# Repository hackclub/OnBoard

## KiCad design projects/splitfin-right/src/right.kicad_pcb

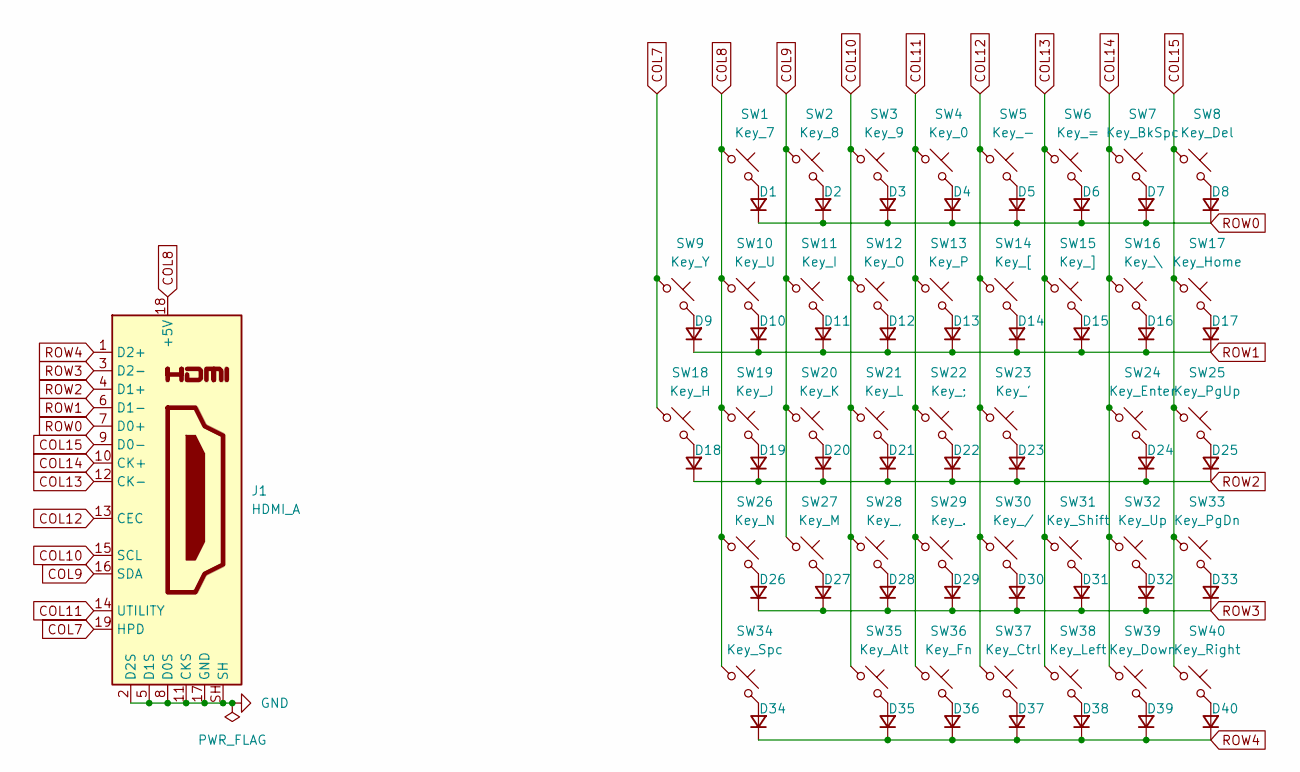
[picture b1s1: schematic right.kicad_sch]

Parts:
D1, D2, D3, D4, D5, D6, D7, D8, D9, D10, D11, D12, D13, D14, D15, D16, D17, D18, D19, D20, D21, D22, D23, D24, D25, D26, D27, D28, D29, D30, D31, D32, D33, D34, D35, D36, D37, D38, D39, D40: D_SOD-123
J1: HDMI_A; HDMI_A_Amphenol_10029449-x01xLF_Horizontal
SW1: Key_7; SW_Gateron_LowProfile_HotSwap_Good
SW2: Key_8; SW_Gateron_LowProfile_HotSwap_Good
SW3: Key_9; SW_Gateron_LowProfile_HotSwap_Good
SW4: Key_0; SW_Gateron_LowProfile_HotSwap_Good
SW5: Key_-; SW_Gateron_LowProfile_HotSwap_Good
SW6: Key_=; SW_Gateron_LowProfile_HotSwap_Good
SW7: Key_BkSpc; SW_Gateron_LowProfile_HotSwap_Good
SW8: Key_Del; SW_Gateron_LowProfile_HotSwap_Good
SW9: Key_Y; SW_Gateron_LowProfile_HotSwap_Good
SW10: Key_U; SW_Gateron_LowProfile_HotSwap_Good
SW11: Key_I; SW_Gateron_LowProfile_HotSwap_Good
SW12: Key_O; SW_Gateron_LowProfile_HotSwap_Good
SW13: Key_P; SW_Gateron_LowProfile_HotSwap_Good
SW14: Key_[; SW_Gateron_LowProfile_HotSwap_Good
SW15: Key_]; SW_Gateron_LowProfile_HotSwap_Good
SW16: Key_\; SW_Gateron_LowProfile_HotSwap_Good
SW17: Key_Home; SW_Gateron_LowProfile_HotSwap_Good
SW18: Key_H; SW_Gateron_LowProfile_HotSwap_Good
SW19: Key_J; SW_Gateron_LowProfile_HotSwap_Good
SW20: Key_K; SW_Gateron_LowProfile_HotSwap_Good
SW21: Key_L; SW_Gateron_LowProfile_HotSwap_Good
SW22: Key_;; SW_Gateron_LowProfile_HotSwap_Good
SW23: Key_'; SW_Gateron_LowProfile_HotSwap_Good
SW24: Key_Enter; SW_Gateron_LowProfile_HotSwap_Good
SW25: Key_PgUp; SW_Gateron_LowProfile_HotSwap_Good
SW26: Key_N; SW_Gateron_LowProfile_HotSwap_Good
SW27: Key_M; SW_Gateron_LowProfile_HotSwap_Good
SW28: Key_,; SW_Gateron_LowProfile_HotSwap_Good
SW29: Key_.; SW_Gateron_LowProfile_HotSwap_Good
SW30: Key_/; SW_Gateron_LowProfile_HotSwap_Good
SW31: Key_Shift; SW_Gateron_LowProfile_HotSwap_Good
SW32: Key_Up; SW_Gateron_LowProfile_HotSwap_Good
SW33: Key_PgDn; SW_Gateron_LowProfile_HotSwap_Good
SW34: Key_Spc; SW_Gateron_LowProfile_HotSwap_Good
SW35: Key_Alt; SW_Gateron_LowProfile_HotSwap_Good
SW36: Key_Fn; SW_Gateron_LowProfile_HotSwap_Good
SW37: Key_Ctrl; SW_Gateron_LowProfile_HotSwap_Good
SW38: Key_Left; SW_Gateron_LowProfile_HotSwap_Good
SW39: Key_Down; SW_Gateron_LowProfile_HotSwap_Good
SW40: Key_Right; SW_Gateron_LowProfile_HotSwap_Good

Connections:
COL7: J1.19 (HPD), SW9.1, SW18.1
COL8: J1.18 (+5V), SW1.1, SW10.1, SW19.1, SW26.1, SW34.1
COL9: J1.16 (SDA), SW2.1, SW11.1, SW20.1, SW27.1
COL10: J1.15 (SCL), SW3.1, SW12.1, SW21.1, SW28.1, SW35.1
COL11: J1.14 (UTILITY), SW4.1, SW13.1, SW22.1, SW29.1, SW36.1
COL12: J1.13 (CEC), SW5.1, SW14.1, SW23.1, SW30.1, SW37.1
COL13: J1.12 (CK-), SW6.1, SW15.1, SW31.1, SW38.1
COL14: J1.10 (CK+), SW7.1, SW16.1, SW24.1, SW32.1, SW39.1
COL15: J1.9 (D0-), SW8.1, SW17.1, SW25.1, SW33.1, SW40.1
GND: J1.2 (D2S), J1.5 (D1S), J1.8 (D0S), J1.11 (CKS), J1.17 (GND), J1.SH
unnamed: D1.2 (A), SW1.2
unnamed: D2.2 (A), SW2.2
unnamed: D3.2 (A), SW3.2
unnamed: D4.2 (A), SW4.2
unnamed: D5.2 (A), SW5.2
unnamed: D6.2 (A), SW6.2
unnamed: D7.2 (A), SW7.2
unnamed: D8.2 (A), SW8.2
unnamed: D9.2 (A), SW9.2
unnamed: D10.2 (A), SW10.2
unnamed: D11.2 (A), SW11.2
unnamed: D12.2 (A), SW12.2
unnamed: D13.2 (A), SW13.2
unnamed: D14.2 (A), SW14.2
unnamed: D15.2 (A), SW15.2
unnamed: D16.2 (A), SW16.2
unnamed: D17.2 (A), SW17.2
unnamed: D18.2 (A), SW18.2
unnamed: D19.2 (A), SW19.2
unnamed: D20.2 (A), SW20.2
unnamed: D21.2 (A), SW21.2
unnamed: D22.2 (A), SW22.2
unnamed: D23.2 (A), SW23.2
unnamed: D24.2 (A), SW24.2
unnamed: D25.2 (A), SW25.2
unnamed: D26.2 (A), SW26.2
unnamed: D27.2 (A), SW27.2
unnamed: D28.2 (A), SW28.2
unnamed: D29.2 (A), SW29.2
unnamed: D30.2 (A), SW30.2
unnamed: D31.2 (A), SW31.2
unnamed: D32.2 (A), SW32.2
unnamed: D33.2 (A), SW33.2
unnamed: D34.2 (A), SW34.2
unnamed: D35.2 (A), SW35.2
unnamed: D36.2 (A), SW36.2
unnamed: D37.2 (A), SW37.2
unnamed: D38.2 (A), SW38.2
unnamed: D39.2 (A), SW39.2
unnamed: D40.2 (A), SW40.2
ROW0: D1.1 (K), D2.1 (K), D3.1 (K), D4.1 (K), D5.1 (K), D6.1 (K), D7.1 (K), D8.1 (K), J1.7 (D0+)
ROW1: D9.1 (K), D10.1 (K), D11.1 (K), D12.1 (K), D13.1 (K), D14.1 (K), D15.1 (K), D16.1 (K), D17.1 (K), J1.6 (D1-)
ROW2: D18.1 (K), D19.1 (K), D20.1 (K), D21.1 (K), D22.1 (K), D23.1 (K), D24.1 (K), D25.1 (K), J1.4 (D1+)
ROW3: D26.1 (K), D27.1 (K), D28.1 (K), D29.1 (K), D30.1 (K), D31.1 (K), D32.1 (K), D33.1 (K), J1.3 (D2-)
ROW4: D34.1 (K), D35.1 (K), D36.1 (K), D37.1 (K), D38.1 (K), D39.1 (K), D40.1 (K), J1.1 (D2+)

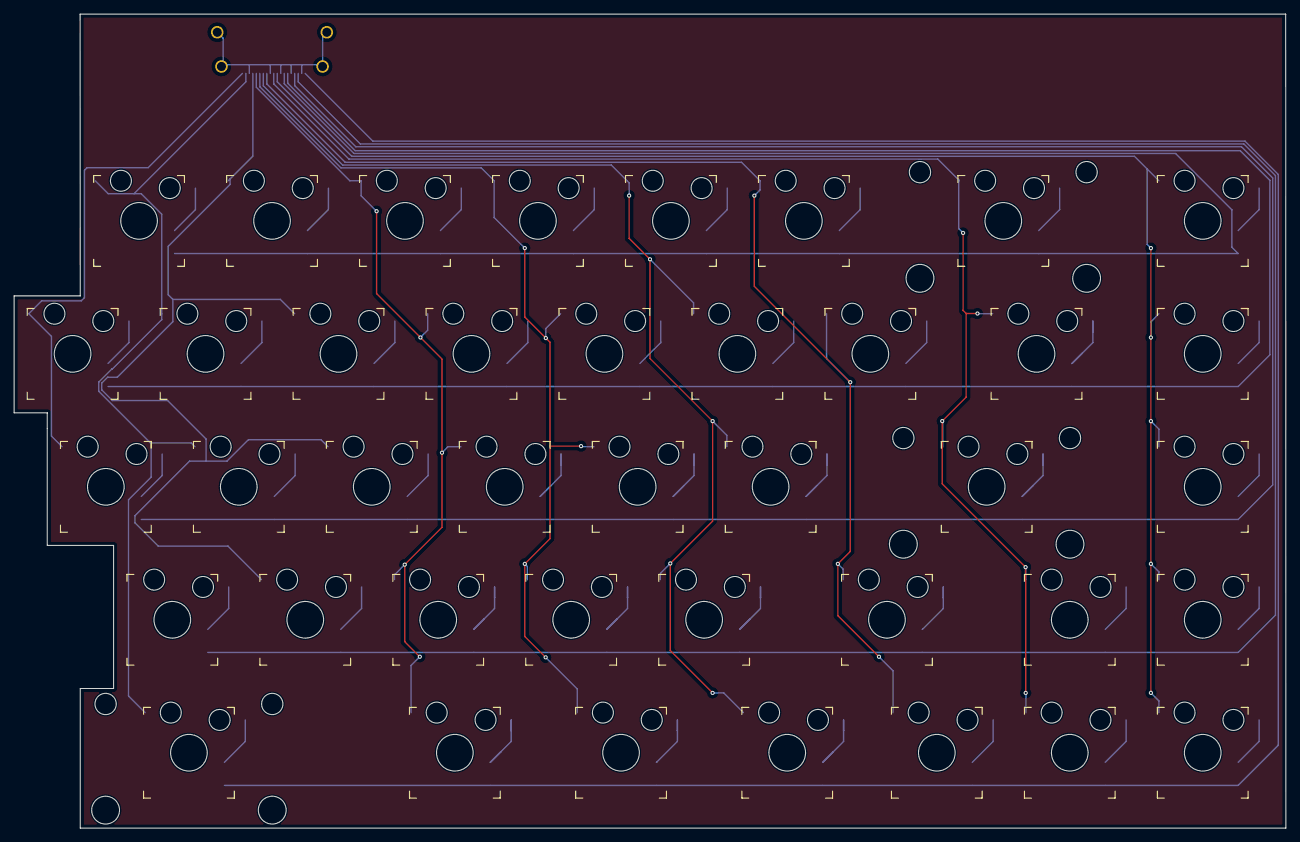
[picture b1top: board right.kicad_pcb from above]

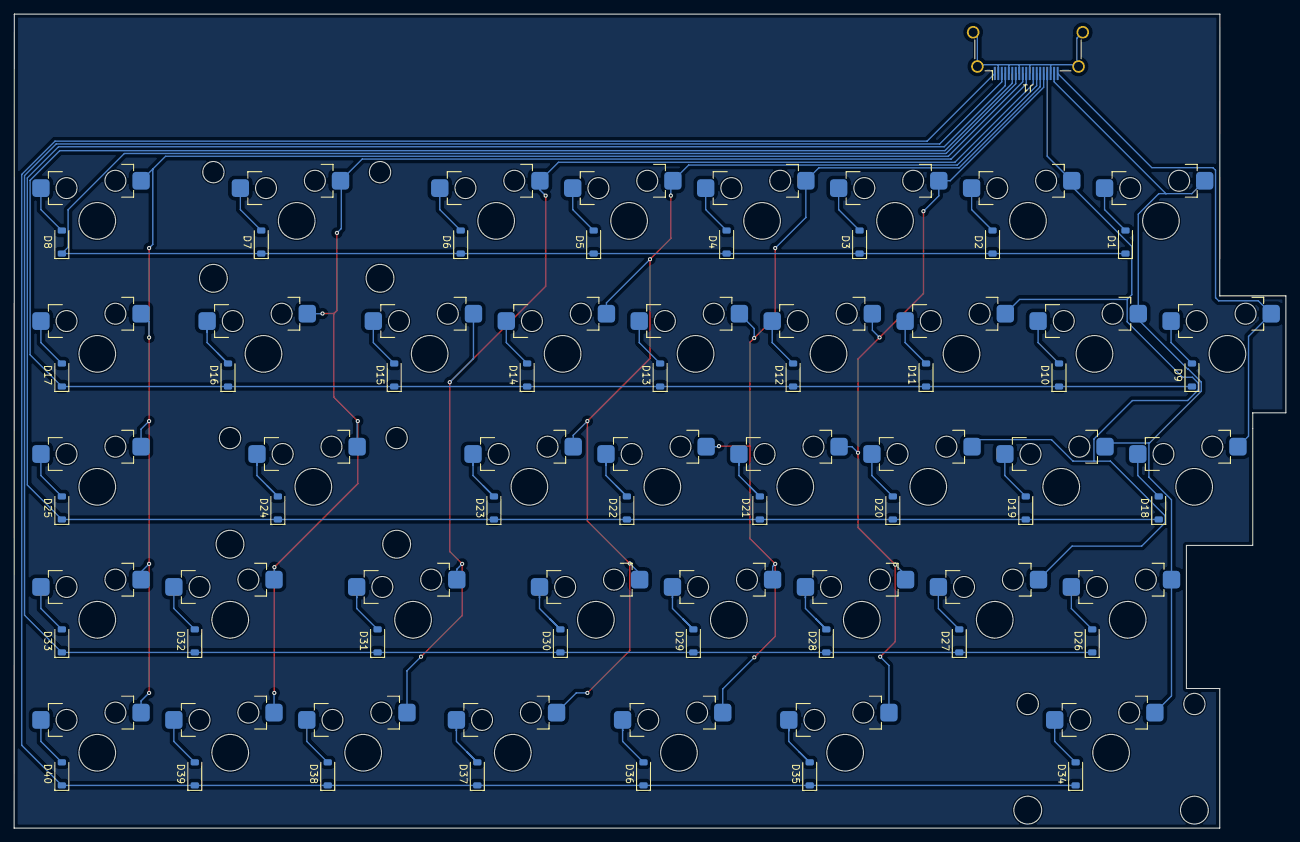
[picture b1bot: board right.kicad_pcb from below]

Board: 2 copper layers, 182.2 x 116.6 mm, 84 parts (41 on the bottom side), 55 nets.

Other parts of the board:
ST7, ST24, ST34: Stabilizer_Cherry_MX_2.00u

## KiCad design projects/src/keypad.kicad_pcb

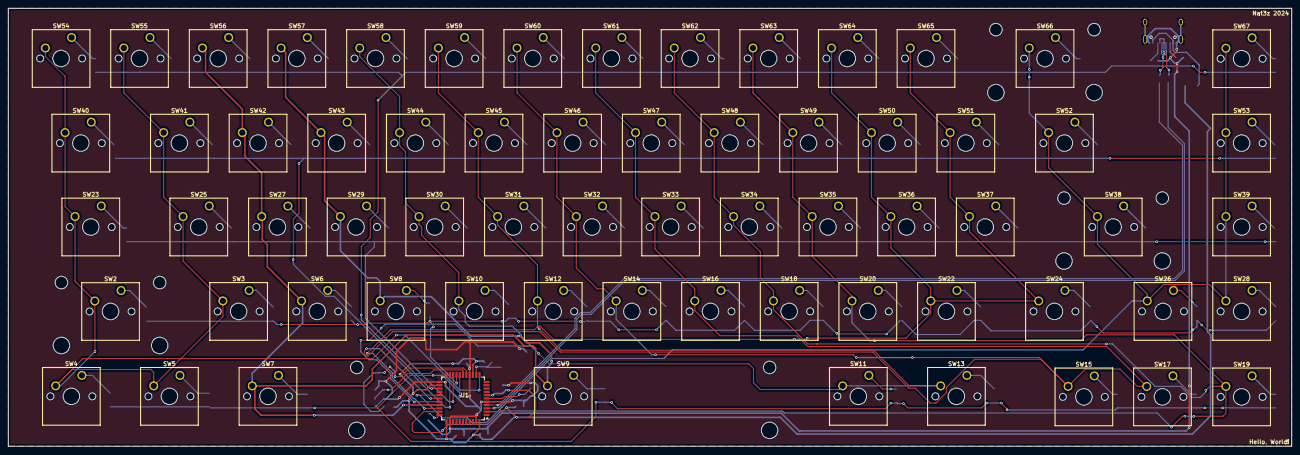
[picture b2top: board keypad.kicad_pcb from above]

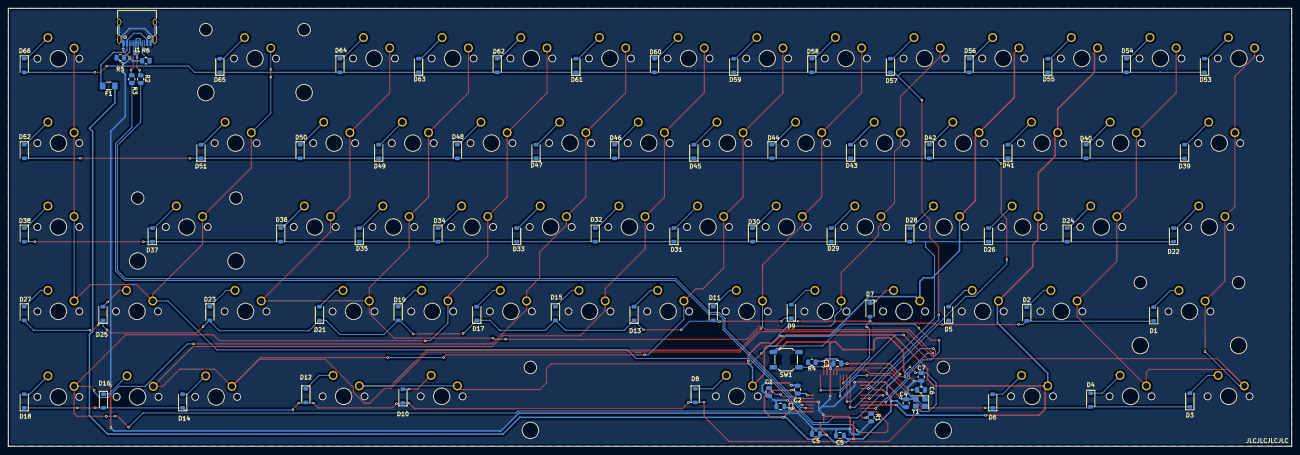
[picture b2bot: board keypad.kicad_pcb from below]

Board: 2 copper layers, 310.8 x 106.1 mm, 150 parts (84 on the bottom side), 90 nets.

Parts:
C1: 1uF; C_0805_2012Metric
C2, C2#2, C3, C4: 0.1uF; C_0805_2012Metric
C5, C5#2: 10uF; C_0805_2012Metric
C6, C7: 22pF; C_0805_2012Metric
D1, D2, D3, D4, D5, D6, D7, D8, D9, D10, D11, D12, D13, D14, D15, D16, D17, D18, D19, D21, D22, D23, D24, D25, D26, D27, D28, D29, D30, D31, D32, D33, D34, D35, D36, D37, D38, D39, D40, D41, D42, D43, D44, D45, D46, D47, D48, D49, D50, D51, D52, D53, D54, D55, D56, D57, D58, D59, D60, D61, D62, D63, D64, D65, D66: D; D_SOD-123
F1: Polyfuse_Small; Fuse_1206_3216Metric_Pad1.42x1.75mm_HandSolder
J1: USB_C_Receptacle; USB_C_Receptacle_HRO_TYPE-C-31-M-12
R1, R4: 10k; R_0805_2012Metric
R2, R3: 22; R_0805_2012Metric
R5, R6: 5.1k; R_0805_2012Metric
SW1: SW_Push; SW_SPST_SKQG_WithStem
SW2, SW38: SW_Push; SW_Cherry_MX_2.25u_PCB
SW3, SW6, SW8, SW10, SW12, SW14, SW15, SW16, SW17, SW18, SW19, SW20, SW22, SW25, SW26, SW27, SW28, SW29, SW30, SW31, SW32, SW33, SW34, SW35, SW36, SW37, SW39, SW41, SW42, SW43, SW44, SW45, SW46, SW47, SW48, SW49, SW50, SW51, SW53, SW54, SW55, SW56, SW57, SW58, SW59, SW60, SW61, SW62, SW63, SW64, SW65, SW67: SW_Push; SW_Cherry_MX_1.00u_PCB
SW4, SW5, SW7, SW11, SW13: SW_Push; SW_Cherry_MX_1.25u_PCB
SW9: SW_Push; SW_Cherry_MX_6.25u_PCB
SW23, SW24: SW_Push; SW_Cherry_MX_1.75u_PCB
SW40, SW52: SW_Push; SW_Cherry_MX_1.50u_PCB
SW66: SW_Push; SW_Cherry_MX_2.00u_PCB
U1: ATmega32U4-A; TQFP-44_10x10mm_P0.8mm
Y1: 16MHz; Crystal_SMD_3225-4Pin_3.2x2.5mm

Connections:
+5V: C2.1, C2#2.1, C3.1, C4.1, C5.1, C5#2.1, F1.1, R4.1, U1.2 (UVCC), U1.7 (VBUS), U1.14 (VCC), U1.24 (AVCC), U1.34 (VCC), U1.44 (AVCC)
COL0: SW2.2, SW3.2, SW4.2, SW5.2, SW23.2, SW25.2, SW40.2, SW41.2, SW54.2, SW55.2, U1.12 (PB7)
COL1: D22.1 (K), D24.2 (A), D26.1 (K), D28.2 (A), D29.1 (K), D30.2 (A), D31.1 (K), D32.2 (A), D33.1 (K), D34.2 (A), D35.1 (K), D36.2 (A), D37.1 (K), D38.2 (A), SW6.2, SW7.2, SW8.2, SW9.2, SW27.2, SW29.2, SW42.2, SW43.2, SW56.2, SW57.2, U1.20 (PD2), U1.30 (PB6)
COL2: SW10.2, SW11.2, SW12.2, SW13.2, SW30.2, SW31.2, SW44.2, SW45.2, SW58.2, SW59.2, U1.29 (PB5)
COL3: SW14.2, SW15.2, SW16.2, SW17.2, SW32.2, SW33.2, SW46.2, SW47.2, SW60.2, SW61.2, U1.28 (PB4)
COL4: SW18.2, SW19.2, SW20.2, SW34.2, SW35.2, SW48.2, SW49.2, SW62.2, SW63.2, U1.32 (PC7)
COL5: SW22.2, SW24.2, SW36.2, SW37.2, SW50.2, SW51.2, SW64.2, SW65.2, U1.31 (PC6)
COL6: SW26.2, SW28.2, SW38.2, SW39.2, SW52.2, SW53.2, SW66.2, SW67.2, U1.27 (PD7)
D+: J1.A6 (D+), J1.B6 (D+), R2.1
D-: J1.A7 (D-), J1.B7 (D-), R3.1
GND: C1.2, C2.2, C2#2.2, C3.2, C4.2, C5.2, C5#2.2, C6.1, C7.1, J1.A1 (GND), J1.A12 (GND), J1.B1 (GND), J1.B12 (GND), J1.S1 (SHIELD), R1.2, R5.2, R6.2, SW1.1, U1.5 (UGND), U1.15 (GND), U1.23 (GND), U1.35 (GND), U1.43 (GND), Y1.2, Y1.4
unnamed: D1.2 (A), SW2.1
unnamed: D2.1 (K), SW3.1
unnamed: D3.2 (A), SW4.1
unnamed: D4.1 (K), SW5.1
unnamed: D5.2 (A), SW6.1
unnamed: D6.2 (A), SW7.1
unnamed: D7.1 (K), SW8.1
unnamed: D8.1 (K), SW9.1
unnamed: D9.2 (A), SW10.1
unnamed: D10.2 (A), SW11.1
unnamed: D11.1 (K), SW12.1
unnamed: D12.1 (K), SW13.1
unnamed: D13.2 (A), SW14.1
unnamed: D14.2 (A), SW15.1
unnamed: D15.1 (K), SW16.1
unnamed: D16.1 (K), SW17.1
unnamed: D17.2 (A), SW18.1
unnamed: D18.2 (A), SW19.1
unnamed: D19.1 (K), SW20.1
unnamed: D21.2 (A), SW22.1
unnamed: D22.2 (A), SW23.1
unnamed: D23.1 (K), SW24.1
unnamed: D24.1 (K), SW25.1
unnamed: D25.2 (A), SW26.1
unnamed: D26.2 (A), SW27.1
unnamed: D27.1 (K), SW28.1
unnamed: D28.1 (K), SW29.1
unnamed: D29.2 (A), SW30.1
unnamed: D30.1 (K), SW31.1
unnamed: D31.2 (A), SW32.1
unnamed: D32.1 (K), SW33.1
unnamed: D33.2 (A), SW34.1
unnamed: D34.1 (K), SW35.1
unnamed: D35.2 (A), SW36.1
unnamed: D36.1 (K), SW37.1
unnamed: D37.2 (A), SW38.1
unnamed: D38.1 (K), SW39.1
unnamed: D39.2 (A), SW40.1
unnamed: D40.1 (K), SW41.1
unnamed: D41.2 (A), SW42.1
unnamed: D42.1 (K), SW43.1
unnamed: D43.2 (A), SW44.1
unnamed: D44.1 (K), SW45.1
unnamed: D45.2 (A), SW46.1
unnamed: D46.1 (K), SW47.1
unnamed: D47.2 (A), SW48.1
unnamed: D48.1 (K), SW49.1
unnamed: D49.2 (A), SW50.1
unnamed: D50.1 (K), SW51.1
unnamed: D51.2 (A), SW52.1
unnamed: D52.1 (K), SW53.1
unnamed: D53.2 (A), SW54.1
unnamed: D54.1 (K), SW55.1
unnamed: D55.2 (A), SW56.1
unnamed: D56.1 (K), SW57.1
unnamed: D57.2 (A), SW58.1
unnamed: D58.1 (K), SW59.1
unnamed: D59.2 (A), SW60.1
unnamed: D60.1 (K), SW61.1
unnamed: D61.2 (A), SW62.1
unnamed: D62.1 (K), SW63.1
unnamed: D63.2 (A), SW64.1
unnamed: D64.1 (K), SW65.1
unnamed: D65.2 (A), SW66.1
unnamed: D66.1 (K), SW67.1
unnamed: F1.2, J1.A4 (VBUS), J1.A9 (VBUS), J1.B4 (VBUS), J1.B9 (VBUS)
unnamed: J1.A5 (CC1), R6.1
unnamed: J1.B5 (CC2), R5.1
unnamed: R2.2, U1.4 (D+)
unnamed: R3.2, U1.3 (D-)
unnamed: C1.1, U1.6 (UCAP)
unnamed: C6.2, U1.17 (XTAL1), Y1.1
unnamed: C7.2, U1.16 (XTAL2), Y1.3
unnamed: R1.1, U1.33 (~HWB/PE2)
unnamed: R4.2, SW1.2, U1.13 (~RESET)
ROW0: D3.1 (K), D4.2 (A), D6.1 (K), D8.2 (A), D10.1 (K), D12.2 (A), D14.1 (K), D16.2 (A), D18.1 (K), U1.18 (PD0)
ROW1: D1.1 (K), D2.2 (A), D5.1 (K), D7.2 (A), D9.1 (K), D11.2 (A), D13.1 (K), D15.2 (A), D17.1 (K), D19.2 (A), D21.1 (K), D23.2 (A), D25.1 (K), D27.2 (A), U1.19 (PD1)
ROW3: D39.1 (K), D40.2 (A), D41.1 (K), D42.2 (A), D43.1 (K), D44.2 (A), D45.1 (K), D46.2 (A), D47.1 (K), D48.2 (A), D49.1 (K), D50.2 (A), D51.1 (K), D52.2 (A), U1.21 (PD3)
ROW4: D53.1 (K), D54.2 (A), D55.1 (K), D56.2 (A), D57.1 (K), D58.2 (A), D59.1 (K), D60.2 (A), D61.1 (K), D62.2 (A), D63.1 (K), D64.2 (A), D65.1 (K), D66.2 (A), U1.25 (PD4)

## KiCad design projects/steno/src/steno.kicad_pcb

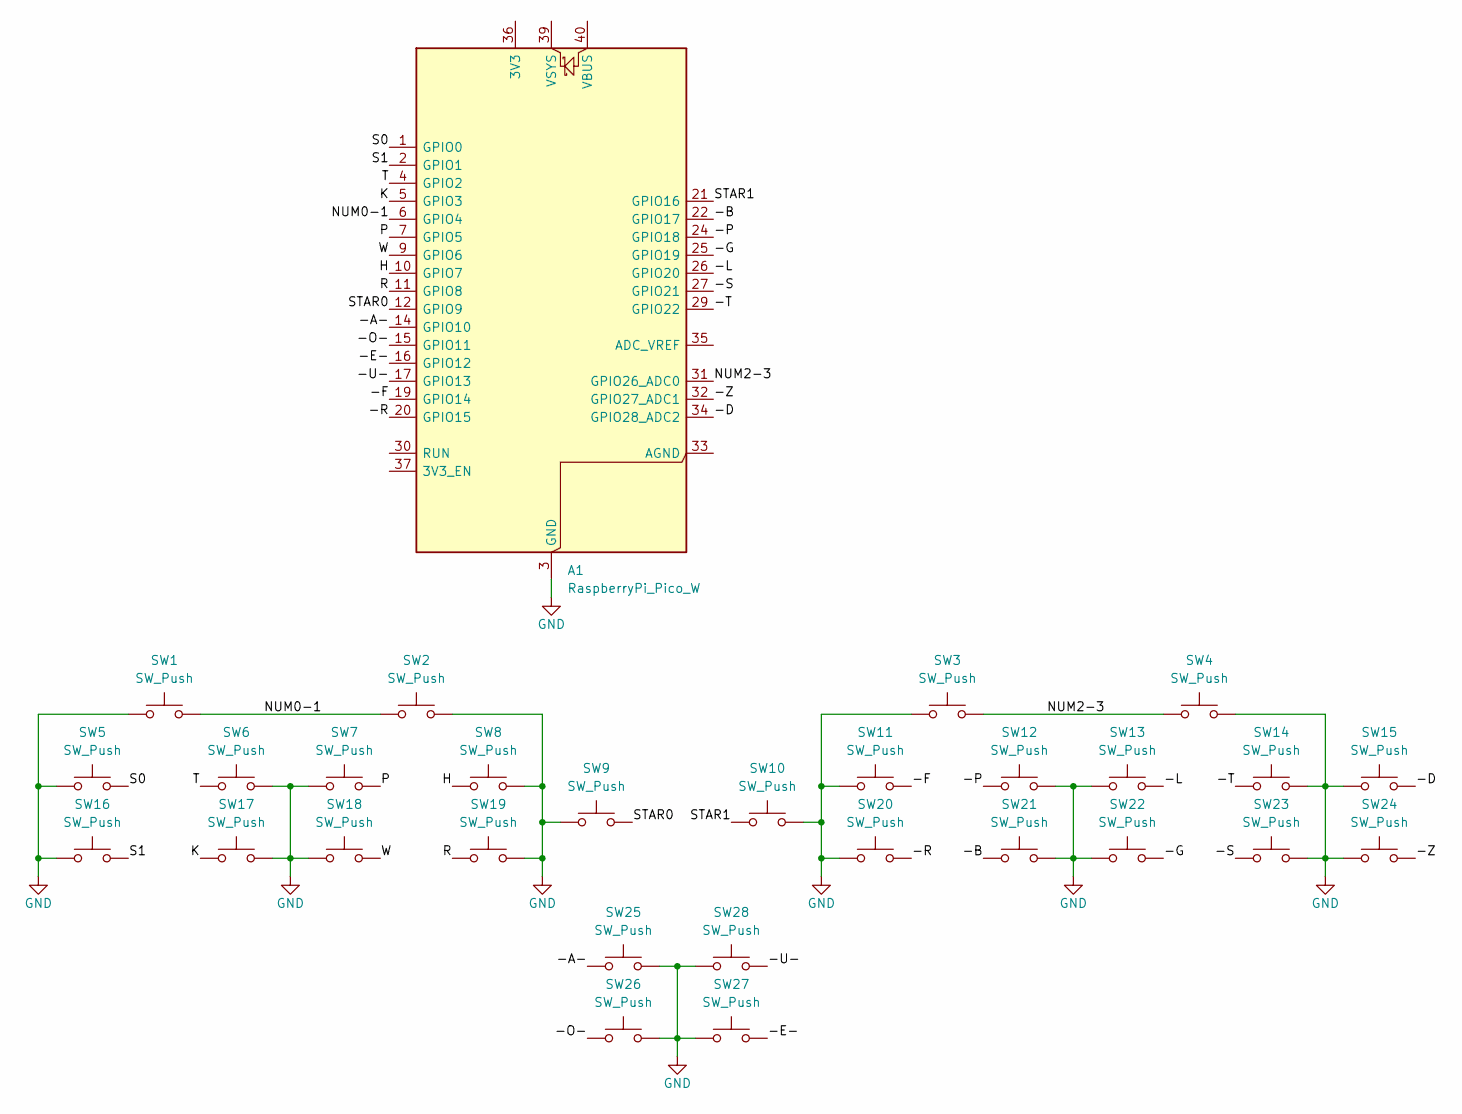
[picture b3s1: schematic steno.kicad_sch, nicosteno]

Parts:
A1: RaspberryPi_Pico_W; RaspberryPi_Pico_Common
SW1, SW2, SW3, SW4, SW9, SW10: SW_Push; SW_Cherry_MX_2.00u_PCB
SW5, SW6, SW7, SW8, SW11, SW12, SW13, SW14, SW15, SW16, SW17, SW18, SW19, SW20, SW21, SW22, SW23, SW24, SW25, SW26, SW27, SW28: SW_Push; SW_Cherry_MX_1.00u_PCB

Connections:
/-A-: A1.14 (GPIO10), SW25.2
/-B: A1.22 (GPIO17), SW21.2
/-D: A1.34 (GPIO28_ADC2), SW15.2
/-E-: A1.16 (GPIO12), SW27.2
/-F: A1.19 (GPIO14), SW11.2
/-G: A1.25 (GPIO19), SW22.2
/-L: A1.26 (GPIO20), SW13.2
/-O-: A1.15 (GPIO11), SW26.2
/-P: A1.24 (GPIO18), SW12.2
/-R: A1.20 (GPIO15), SW20.2
/-S: A1.27 (GPIO21), SW23.2
/-T: A1.29 (GPIO22), SW14.2
/-U-: A1.17 (GPIO13), SW28.2
/-Z: A1.32 (GPIO27_ADC1), SW24.2
/H: A1.10 (GPIO7), SW8.2
/K: A1.5 (GPIO3), SW17.2
/NUM0-1: A1.6 (GPIO4), SW1.2, SW2.2
/NUM2-3: A1.31 (GPIO26_ADC0), SW3.2, SW4.2
/P: A1.7 (GPIO5), SW7.2
/R: A1.11 (GPIO8), SW19.2
/S0: A1.1 (GPIO0), SW5.2
/S1: A1.2 (GPIO1), SW16.2
/STAR0: A1.12 (GPIO9), SW9.2
/STAR1: A1.21 (GPIO16), SW10.2
/T: A1.4 (GPIO2), SW6.2
/W: A1.9 (GPIO6), SW18.2
GND: A1.3 (GND), A1.8 (GND), A1.13 (GND), A1.18 (GND), A1.23 (GND), A1.28 (GND), A1.38 (GND), SW1.1, SW2.1, SW3.1, SW4.1, SW5.1, SW6.1, SW7.1, SW8.1, SW9.1, SW10.1, SW11.1, SW12.1, SW13.1, SW14.1, SW15.1, SW16.1, SW17.1, SW18.1, SW19.1, SW20.1, SW21.1, SW22.1, SW23.1, SW24.1, SW25.1, SW26.1, SW27.1, SW28.1

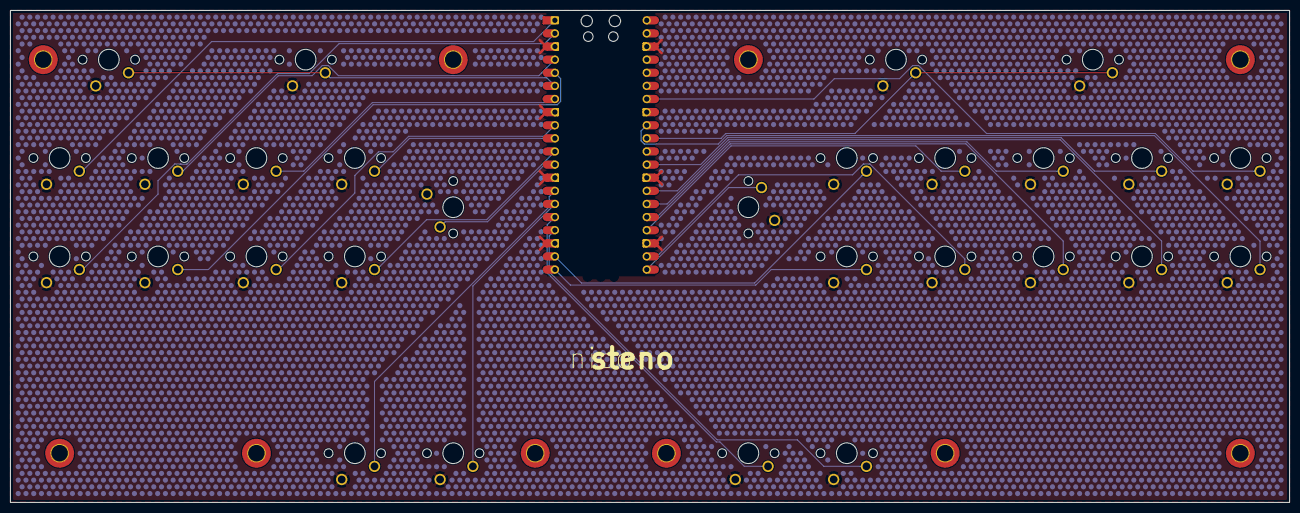
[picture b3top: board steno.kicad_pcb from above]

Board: 2 copper layers, 247.6 x 95.3 mm, 29 parts (0 on the bottom side), 27 nets.

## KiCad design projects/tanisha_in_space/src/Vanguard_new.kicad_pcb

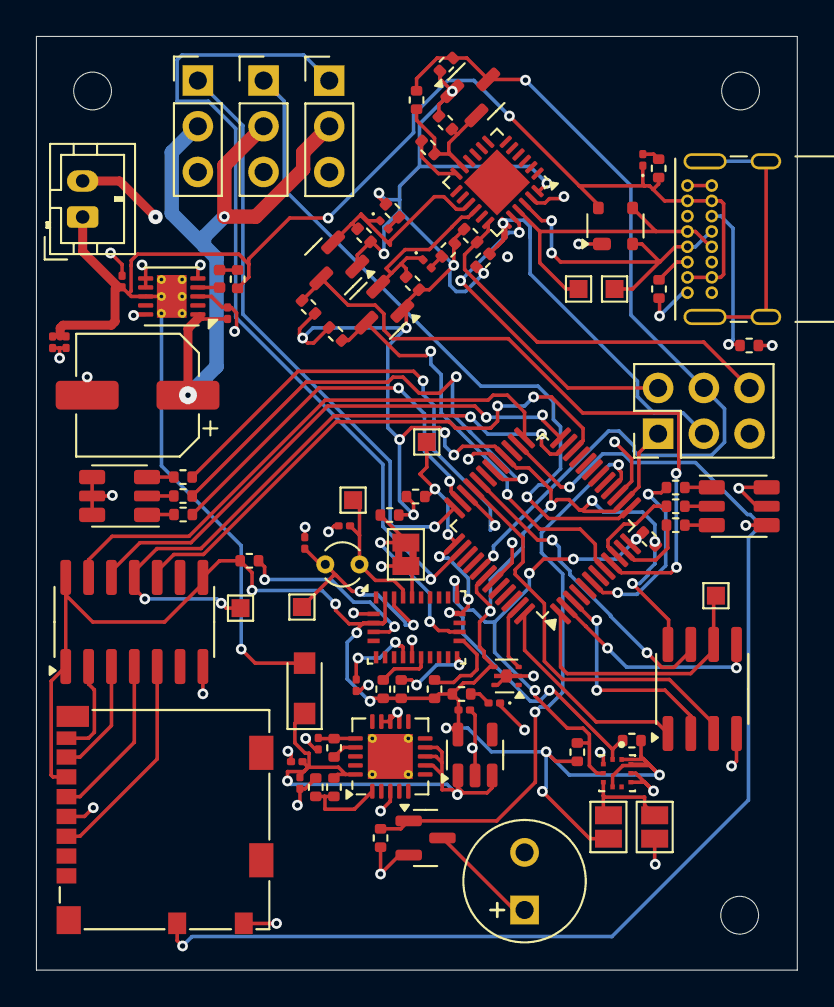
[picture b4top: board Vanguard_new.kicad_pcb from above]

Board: 4 copper layers, 42.3 x 51.9 mm, 90 parts (0 on the bottom side), 72 nets.

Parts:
ADR1: SolderJumper-2_P1.3mm_Bridged2Bar_Pad1.0x1.5mm
BZ1: Buzzer; MagneticBuzzer_Kingstate_KCG0601
C2, C3: 22p; C_0201_0603Metric
C4, C5: 22u; C_0201_0603Metric
C6, C11: 1u; C_0201_0603Metric
C7: 0u1; C_0201_0603Metric
C8: 10u; C_0201_0603Metric
C9: 2u2; C_0201_0603Metric
C10: 100u; CP_Elec_6.3x5.4
C12: 4n7; C_0201_0603Metric
C13: 100n; C_0201_0603Metric
D1: PRTR5V0U2X; SOT-143
D2, D3, D7: LED; LED_0201_0603Metric
D5: GREEN; LED_0201_0603Metric
D6: PMEG6020ER; Nexperia_CFP3_SOD-123W
J1: USB_C_Receptacle_USB2.0_16P; USB_C_Receptacle_GCT_USB4085
J2: Conn_02x03_Pin; PinHeader_2x03_P2.54mm_Vertical
J3: Micro_SD_Card_Det1; microSD_HC_Molex_104031-0811
J4: STARBOARD_SERVO; PinHeader_1x03_P2.54mm_Vertical
J5: PORTSIDE_SERVO; PinHeader_1x03_P2.54mm_Vertical
J6: Battery In; JST_PH_B2B-PH-K_1x02_P2.00mm_Vertical
J7: EJECTION_SERVO; PinHeader_1x03_P2.54mm_Vertical
JP1, JP2: Jumper_2_Small_Open; SolderJumper-2_P1.3mm_Open_Pad1.0x1.5mm
L1: 6u8; L_0402_1005Metric
PORTSIDE_RGB1: SMLVN6RGB; LED_ROHM_SMLVN6
Q1, Q2, Q3, Q4: BSS138; SOT-23
R1, R36: 4.7kΩ; R_0402_1005Metric
R2, R6, R7, R9, R10, R11, R12, R13, R19, R20: 4k7; R_0402_1005Metric
R3, R4: 330; R_0402_1005Metric
R5: 0; R_0402_1005Metric
R8: DNP; R_0402_1005Metric
R14, R15: 100k; R_0402_1005Metric
R16: 19k1; R_0402_1005Metric
R17: 330R; R_0402_1005Metric
R18, R23, R24: 10k; R_0402_1005Metric
R21, R22, R34: 2k2; R_0402_1005Metric
R25, R26, R27, R28, R29, R30: 220; R_0402_1005Metric
R31, R32: 5k1; R_0402_1005Metric
R33: 5m; R_0402_1005Metric
R35: R220; R_0402_1005Metric
STARBOARD_RGB1: SMLVN6RGB; LED_ROHM_SMLVN6
TP1, TP2, TP3, TP4, TP5, TP6, TP7: TestPoint; TestPoint_Pad_1.0x1.0mm
U1: ATSAMD11D14A-M; QFN-24-1EP_4x4mm_P0.5mm_EP2.6x2.6mm
U2: ATmega4809-A; TQFP-48_7x7mm_P0.5mm
U3: AT25DF641A-SH-T; SOIC-8_3.9x4.9mm_P1.27mm
U4: AP2112K-3.3; SOT-23-5
U5: BD1020HFV; HVSOF5
U6: BNO086; LGA-28_5.2x3.8mm_P0.5mm
U7: TXB0104D; SOIC-14_3.9x8.7mm_P1.27mm
U8: TPS61092; DFN-10-1EP_3x3mm_P0.5mm_EP1.65x2.38mm_ThermalVias
U9: MPM3610AGQV-P; QFN-20-1EP_4x4mm_P0.5mm_EP2.5x2.5mm_ThermalVias
U10: BMP390L; XDCR_BMP390L
Y1: 32.768kHz; Crystal_C26-LF_D2.1mm_L6.5mm_Vertical

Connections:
+3.3V: C6.1, J2.1, J3.6 (VSS), JP2.2 (B), Q1.1 (G), Q2.1 (G), Q3.1 (G), R1.1, R2.1, R3.1, R4.1, R6.1, R7.1, R9.1, R10.1, R11.1, R12.1, R13.1, R17.1, R18.2, R19.2, R20.2, R21.1, R22.1, R23.1, R24.1, R36.1, U1.24 (VDD), U2.14 (VCC), U2.28 (AVCC), U2.42 (VCC), U3.8 (VCC), U4.5 (VOUT), U5.4 (VDD), U6.3 (VDD), U6.28 (VDDIO), U7.1 (VCCA), U7.8 (OE), U7.14 (VCCB), U10.1 (VDDIO), U10.6 (~CS), U10.10 (VDD)
+5V: C9.1, C10.1, J4.2, J5.2, J7.2, U8.1 (VOUT)
/RX_UPDI: R5.1, U1.12 (PA15)
/TX_UPDI: Q1.2 (S), R5.2, R6.2, R8.1, U1.11 (PA14)
BATT_IN: C8.1, C12.1, C13.1, D1.4 (VCC), D6.2 (A), D7.1 (K), J1.A4 (VBUS), J1.A9 (VBUS), J1.B4 (VBUS), J1.B9 (VBUS), J6.1, R33.2, R35.2, U8.8 (VBAT), U8.11 (EN)
BUZZER: Q4.1 (G), R34.1, U2.16 (PC4)
CD: J3.9 (DET), U2.26 (PD6)
D4: TP3.1, U2.23 (PD3), U7.11 (B3)
D5: U2.22 (PD2), U7.10 (B4)
D6: U2.24 (PD4), U7.12 (B2)
D7: U2.25 (PD5), U7.13 (B1)
EJEC_SERVO: J7.1, U2.38 (PF4)
GND: ADR1.1 (A), BZ1.2 (-), C2.2, C3.2, C4.2, C5.2, C6.2, C7.2, C8.2, C9.2, C10.2, C11.2, C12.2, C13.2, D1.1 (GND), D5.1 (K), J1.A1 (GND), J1.A12 (GND), J1.B1 (GND), J1.B12 (GND), J2.5, J3.4 (VDD), J3.10 (SHIELD), J4.3, J5.3, J6.2, J7.3, JP1.2 (B), PORTSIDE_RGB1.4 (GK), PORTSIDE_RGB1.5 (RK), PORTSIDE_RGB1.6 (BK), Q4.2 (S), R16.2, R31.2, R32.2, R34.2, STARBOARD_RGB1.4 (GK), STARBOARD_RGB1.5 (RK), STARBOARD_RGB1.6 (BK), U1.23 (GND), U2.15 (GND), U2.29 (GND), U2.43 (GND), U3.4 (GND), U4.2 (GND), U5.2 (PG), U5.5 (GND), U6.2 (GND), U6.10 (CLKSEL0), U6.25 (GNDIO), U7.7 (GND), U8.3 (SW), U8.5 (PGND), U8.6 (PGND), U8.7 (PGND), U8.10 (SYNC), U9.3 (AGND), U9.12 (PGND), U9.13 (PGND), U9.14 (PGND), U10.3 (VSS/GND), U10.8 (VSS/GND), U10.9 (VSS/GND)
HOLD: U2.32 (PE2), U3.7 (~HOLD)
unnamed: ADR1.2 (B), R23.2, U6.17 (SA0/H_MOSI)
unnamed: BZ1.1 (+), Q4.3 (D)
unnamed: D1.2 (I/O1), J1.A6 (D+), J1.B6 (D+), TP1.1, U1.22 (PA25)
unnamed: D1.3 (I/O2), J1.A7 (D-), J1.B7 (D-), TP2.1, U1.21 (PA24)
unnamed: D2.2 (A), R4.2
unnamed: D2.1 (K), Q3.2 (S), R9.2, U1.15 (PA22)
unnamed: D3.2 (A), R3.2
unnamed: D3.1 (K), Q2.2 (S), R10.2, U1.16 (PA23)
unnamed: D5.2 (A), R17.2
unnamed: C5.1, C11.1, D6.1 (K), R15.1, U4.1 (VIN), U4.3 (EN), U9.7 (OUT), U9.8 (OUT), U9.9 (OUT), U9.20 (OUT)
unnamed: D7.2 (A), R35.1
unnamed: J1.A5 (CC1), R31.1
unnamed: J1.B5 (CC2), R32.1
unnamed: J2.2, U1.20 (PA31/SWDIO)
unnamed: J2.3, R2.2, U1.19 (PA30/SWCLK)
unnamed: J2.6, R11.2, U1.18 (PA28/~RST)
unnamed: J3.5 (CLK), U7.4 (A3)
unnamed: J3.3 (CMD), U7.5 (A4)
unnamed: J3.7 (DAT0), U7.3 (A2)
unnamed: J3.8 (DAT1), U7.2 (A1)
unnamed: JP1.1 (A), JP2.1 (A), U10.5 (SDO/DNC/SA0)
unnamed: L1.1, R33.1
unnamed: L1.2, U8.4 (SW)
unnamed: PORTSIDE_RGB1.1 (BA), R28.1
unnamed: PORTSIDE_RGB1.3 (GA), R30.1
unnamed: PORTSIDE_RGB1.2 (RA), R29.1
unnamed: R25.2, STARBOARD_RGB1.1 (BA)
unnamed: R27.2, STARBOARD_RGB1.3 (GA)
unnamed: R26.2, STARBOARD_RGB1.2 (RA)
unnamed: C7.1, U6.9 (CAP)
unnamed: R19.1, U6.15 (ENV_SCL)
unnamed: R20.1, U6.16 (ENV_SDA)
unnamed: C3.1, TP5.1, U6.27 (XIN32), Y1.2
unnamed: C2.1, TP6.1, U6.26 (XOUT32/CLKSEL1), Y1.1
unnamed: R24.2, U6.4 (~BOOT)
unnamed: R18.1, U6.11 (~RST)
unnamed: R14.2, U9.17 (EN)
unnamed: R15.2, R16.1, U9.1 (FB)
unnamed: C4.1, R14.1, U9.16 (IN)
PA0/MISO: U2.3 (PA7), U3.2 (SO(SOI))
PA1/MOSI: U2.2 (PA6), U3.5 (SI(SIO))
PA2/SCK: TP4.1, U2.1 (PA5), U3.6 (SCK)
PA3/SS: U2.48 (PA4), U3.1 (~CS)
PORT_BLUE: R28.2, U2.35 (PF1)
PORT_GREEN: R30.2, U2.34 (PF0)
PORT_RED: R29.2, U2.30 (PE0)
PORT_SERVO: J5.1, U2.13 (PC3)
RX0: Q3.3 (D), R12.2, U2.9 (PB5)
SCL: R1.2, R22.2, TP7.1, U2.37 (PF3), U6.19 (H_SCL/SCK/RX), U10.2 (SCK/SCL)
SDA: R21.2, R36.2, U2.12 (PC2), U6.20 (H_SDA/H_MISO/TX), U10.4 (SDI/SDO/SDA)
STAR_BLUE: R25.1, U2.6 (PB2)
STAR_GREEN: R27.1, U2.11 (PC1)
STAR_RED: R26.1, U2.10 (PC0)
STAR_SERVO: J4.1, U2.36 (PF2)
TEMP_SENSOR: U2.47 (PA3), U5.3 (OUT)
TX0: Q2.3 (D), R13.2, U2.8 (PB4)
UPDI: J2.4, Q1.3 (D), R7.2, R8.2, U2.41 (UPDI)
WP: U2.33 (PE3), U3.3 (~WP)

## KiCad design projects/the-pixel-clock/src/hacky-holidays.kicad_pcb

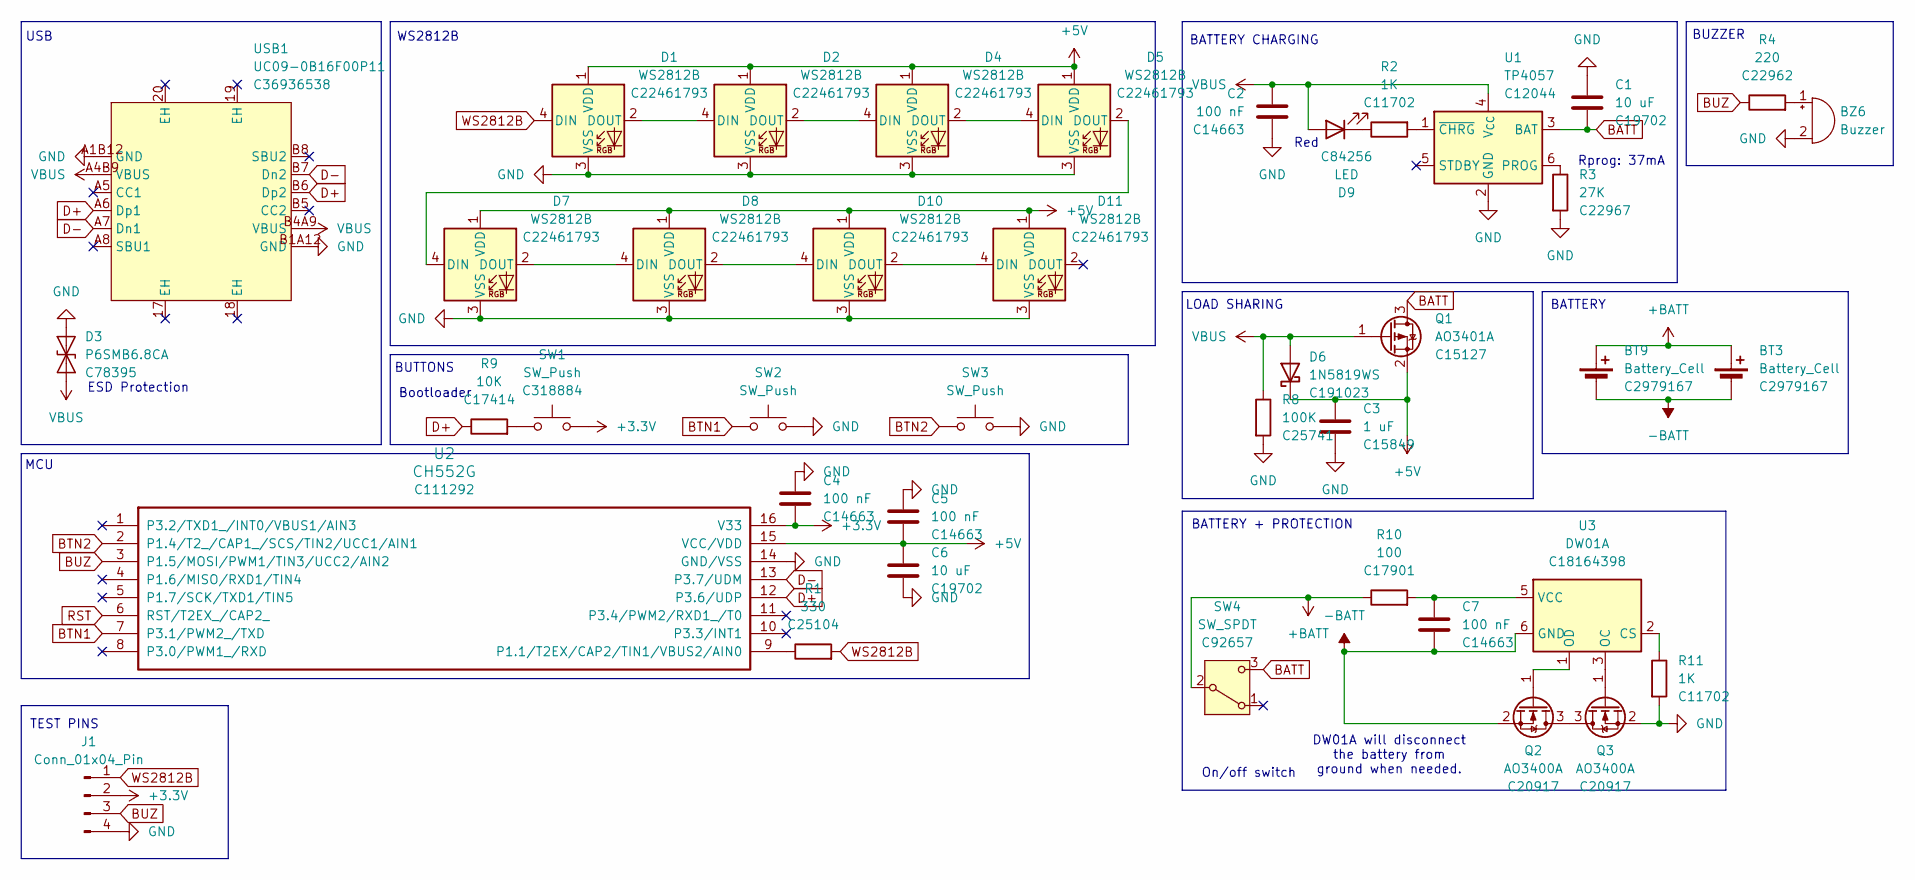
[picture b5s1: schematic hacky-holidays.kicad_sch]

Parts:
BT3, BT9: Battery_Cell; BatteryHolder_MYOUNG_BS-07-A1BJ001_CR2032; LCSC C2979167
BZ6: Buzzer; Buzzer_12x9.5RM7.6
C1, C6: 10 uF; C_0603_1608Metric; LCSC C19702
C2, C4, C5, C7: 100 nF; C_0603_1608Metric; LCSC C14663
C3: 1 uF; C_0603_1608Metric; LCSC C15849
D1, D2, D4, D5, D7, D8, D10, D11: WS2812B; LED_WS2812B_PLCC4_5.0x5.0mm_P3.2mm; LCSC C22461793
D3: P6SMB6.8CA; D_SMB; LCSC C78395
D6: 1N5819WS; D_SOD-323; LCSC C191023
D9: LED; LED_0805_2012Metric; LCSC C84256
J1: Conn_01x04_Pin; PinHeader_1x04_P2.54mm_Vertical
Q1: AO3401A; SOT-23; LCSC C15127
Q2, Q3: AO3400A; SOT-23; LCSC C20917
R1: 330; R_0402_1005Metric; LCSC C25104
R2, R11: 1K; R_0402_1005Metric; LCSC C11702
R3: 27K; R_0603_1608Metric; LCSC C22967
R4: 220; R_0603_1608Metric; LCSC C22962
R8: 100K; R_0402_1005Metric; LCSC C25741
R9: 10K; R_0805_2012Metric; LCSC C17414
R10: 100; R_1206_3216Metric; LCSC C17901
SW1: SW_Push; SW_Push_1P1T_XKB_TS-1187A; LCSC C318884
SW2, SW3: SW_Push; SW_PUSH-12mm
SW4: SW_SPDT; SW-TH_K3-1260D-L1; LCSC C92657
U1: TP4057; SOT-23-6; LCSC C12044
U2: CH552G; STC_SOP-16_3.9x9.9mm_P1.27mm; LCSC C111292
U3: DW01A; SOT-23-6; LCSC C18164398
USB1: UC09-0B16F00P11; USB-C_UC09-0B16F00P11; LCSC Part C36936538

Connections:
+3.3V: C4.2, J1.2, SW1.2, U2.16 (V33)
+5V: C3.1, C5.1, C6.2, D1.1 (VDD), D2.1 (VDD), D4.1 (VDD), D5.1 (VDD), D6.1 (K), D7.1 (VDD), D8.1 (VDD), D10.1 (VDD), D11.1 (VDD), Q1.2 (S), U2.15 (VCC/VDD)
+BATT: BT3.1 (+), BT9.1 (+), R10.1, SW4.2 (B)
-BATT: BT3.2 (-), BT9.2 (-), C7.2, Q2.2 (S), U3.6 (GND)
BATT: C1.2, Q1.3 (D), SW4.3 (C), U1.3 (BAT)
BTN1: SW2.1, U2.7 (P3.1/PWM2_/TXD)
BTN2: SW3.1, U2.2 (P1.4/T2_/CAP1_/SCS/TIN2/UCC1/AIN1)
BUZ: J1.3, R4.1, U2.3 (P1.5/MOSI/PWM1/TIN3/UCC2/AIN2)
D+: R9.1, U2.12 (P3.6/UDP), USB1.A6 (Dp1), USB1.B6 (Dp2)
D-: U2.13 (P3.7/UDM), USB1.A7 (Dn1), USB1.B7 (Dn2)
GND: BZ6.2 (-), C1.1, C2.2, C3.2, C4.1, C5.2, C6.1, D1.3 (VSS), D2.3 (VSS), D3.2 (A2), D4.3 (VSS), D5.3 (VSS), D7.3 (VSS), D8.3 (VSS), D10.3 (VSS), D11.3 (VSS), J1.4, Q3.2 (S), R3.2, R8.2, R11.2, SW2.2, SW3.2, U1.2 (GND), U2.14 (GND/VSS), USB1.A1B12 (GND), USB1.B1A12 (GND)
unnamed: BZ6.1 (+), R4.2
unnamed: D1.2 (DOUT), D2.4 (DIN)
unnamed: D2.2 (DOUT), D4.4 (DIN)
unnamed: D4.2 (DOUT), D5.4 (DIN)
unnamed: D5.2 (DOUT), D7.4 (DIN)
unnamed: D7.2 (DOUT), D8.4 (DIN)
unnamed: D9.1 (K), R2.1
unnamed: D8.2 (DOUT), D10.4 (DIN)
unnamed: D10.2 (DOUT), D11.4 (DIN)
unnamed: Q2.3 (D), Q3.3 (D)
unnamed: Q2.1 (G), U3.1 (OD)
unnamed: Q3.1 (G), U3.3 (OC)
unnamed: R9.2, SW1.1
unnamed: R3.1, U1.6 (PROG)
unnamed: R2.2, U1.1 (~CHRG)
unnamed: R1.1, U2.9 (P1.1/T2EX/CAP2/TIN1/VBUS2/AIN0)
unnamed: R11.1, U3.2 (CS)
unnamed: C7.1, R10.2, U3.5 (VCC)
RST: U2.6 (RST/T2EX_/CAP2_)
VBUS: C2.1, D3.1 (A1), D6.2 (A), D9.2 (A), Q1.1 (G), R8.1, U1.4 (V_{CC}), USB1.A4B9 (VBUS), USB1.B4A9 (VBUS)
WS2812B: D1.4 (DIN), J1.1, R1.2

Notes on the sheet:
Bootloader
On/off switch
MCU
BATTERY
DW01A will disconnect the battery from ground when needed.
Rprog: 37mA
BUZZER
Red
USB
BUTTONS
BATTERY CHARGING
BATTERY + PROTECTION
TEST PINS
LOAD SHARING
WS2812B
ESD Protection
